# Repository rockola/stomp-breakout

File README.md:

# stomp-breakout
3PDT breakout PCB with LED and resistor

* v0.1: initial import, trace between LED anode and resistor missing
* v0.2: board input grounded in bypass
* v0.4: bi-color CA LED (can still use standard LED), optional anti-pop capacitor & resistor

MIT License.

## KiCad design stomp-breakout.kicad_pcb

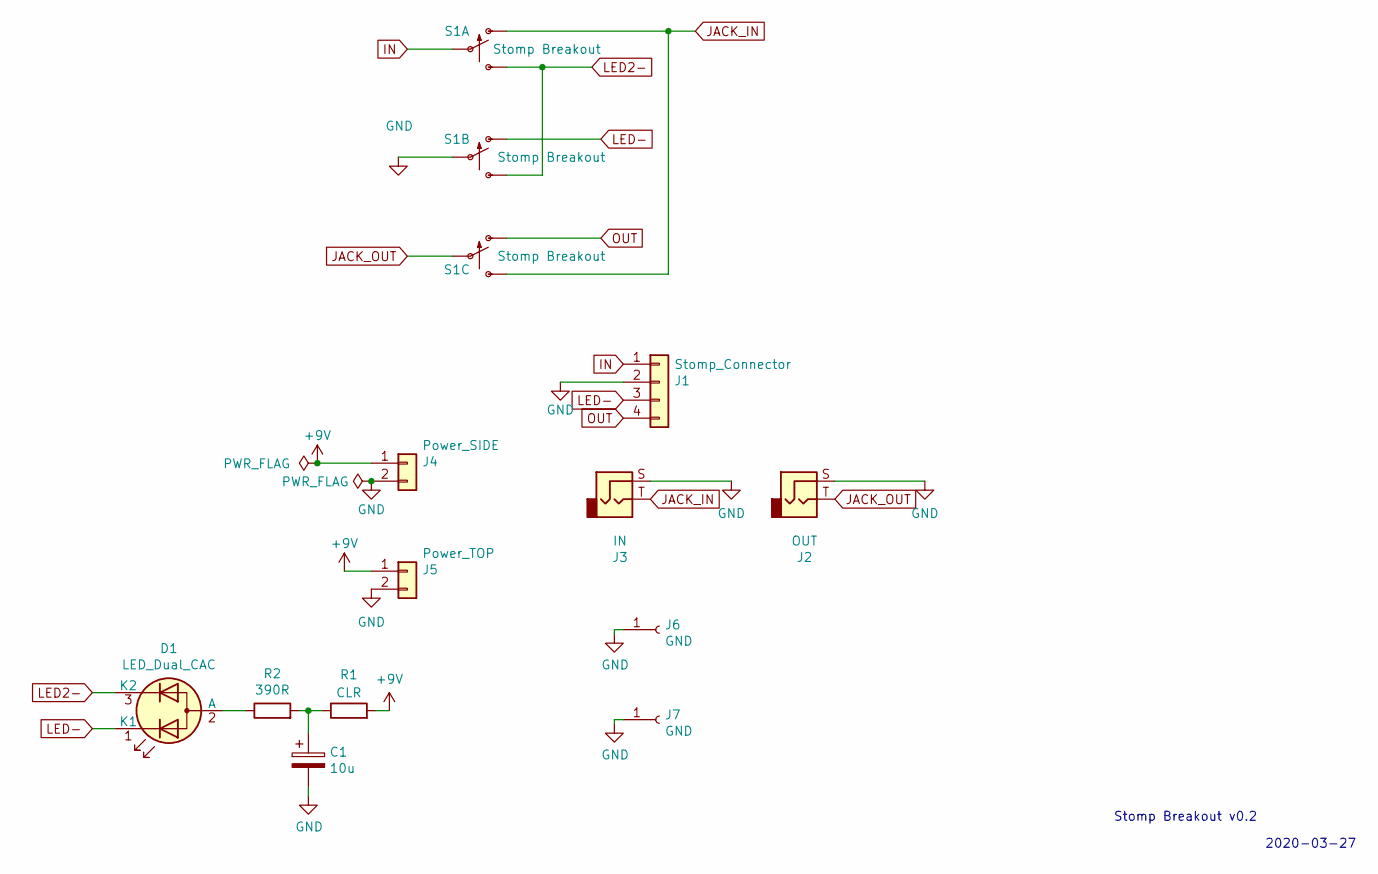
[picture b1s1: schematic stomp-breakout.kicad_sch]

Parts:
C1: 10u; CP_D5.0_P2.50
D1: LED_Dual_CAC; LED_D5.0mm-3
J1: Stomp_Connector; Stomp_4pin_ALT
J2: OUT; 2PADS_TS_Vertical_NOBORDER
J3: IN; 2PADS_TS_Vertical_NOBORDER
J4: Power_SIDE; Power_Header_2pin_VERTICAL_ALT_NOBORDER
J5: Power_TOP; Power_Header_2pin_TOP_ALT_NOBORDER
J6, J7: GND; 1PAD
R1: CLR; Resistor_0.25W_Standing
R2: 390R; Resistor_0.25W_Standing
S1: Stomp Breakout; 3PDT_Stomp

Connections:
+9V: J4.1 (PWR), J5.1 (PWR), R1.2
GND: C1.2, J1.2 (GND), J2.S, J3.S, J4.2 (GND), J5.2 (GND), J6.1, J7.1, S1.5
IN: J1.1 (IN), S1.2
JACK_IN: J3.T, S1.1 (O), S1.9 (S)
JACK_OUT: J2.T, S1.8
LED2-: D1.3 (K2), S1.3 (S), S1.6 (S)
LED-: D1.1 (K1), J1.3 (SW), S1.4 (O)
unnamed: C1.1, R1.1, R2.2
unnamed: D1.2 (A), R2.1
OUT: J1.4 (OUT), S1.7 (O)

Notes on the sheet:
2020-03-27
Stomp Breakout v0.2

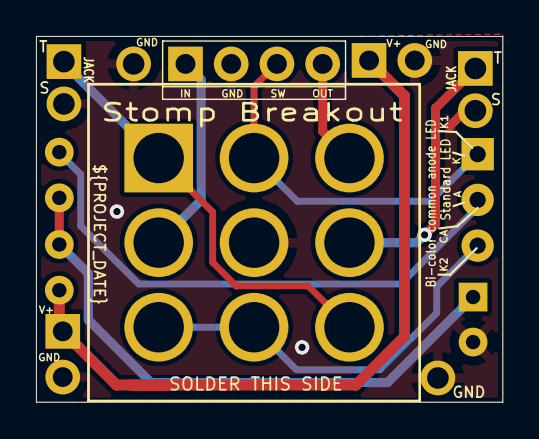
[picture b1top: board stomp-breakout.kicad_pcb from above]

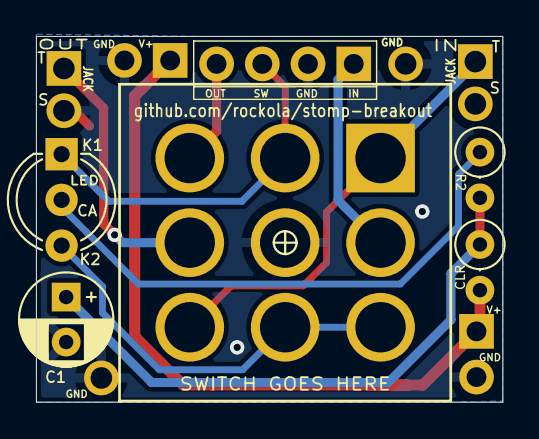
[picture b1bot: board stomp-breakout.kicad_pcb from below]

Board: 2 copper layers, 25.9 x 20.3 mm, 12 parts (4 on the bottom side), 10 nets.

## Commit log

2020-03-14 0.1: initial import
2020-03-14 obsolete
2020-03-14 initial Gerbers
2020-03-14 0.1 board images
2020-03-14 initial version
2020-03-15 0.1: final silkscreen
2020-03-27 v0.2: board input grounded in bypass
2020-05-20 0.4 Gerbers
2020-05-20 0.4 images
2020-05-20 ignore KiCAD v5 backups
2020-05-20 v0.4: optional bicolor CA LED, anti-pop capacitor & resistor
2020-06-06 images of v0.4 pcb
2022-01-11 ignore backups directory
2022-01-11 updated to KiCad 6.0
